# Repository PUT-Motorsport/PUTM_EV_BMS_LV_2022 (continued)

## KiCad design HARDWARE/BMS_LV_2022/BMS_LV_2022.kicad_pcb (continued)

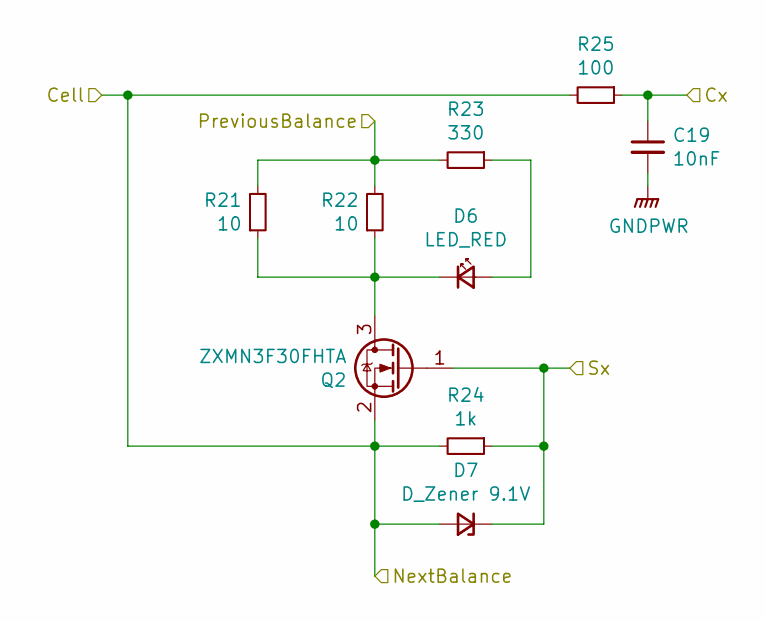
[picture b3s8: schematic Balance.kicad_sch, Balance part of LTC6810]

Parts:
C19: 10nF; C_0603_1608Metric
D6: LED_RED; LED_0603_1608Metric
D7: D_Zener 9.1V; D_SOD-323; Part Number BZX384-C9V1.115
Q2: ZXMN3F30FHTA; SOT-23
R21, R22: 10; R_2512_6332Metric; Part Number CHP2512AFX-10R0ELF
R23: 330; R_0603_1608Metric
R24: 1k; R_0603_1608Metric
R25: 100; R_0603_1608Metric

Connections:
+BATT: R21.2, R22.2, R23.2; also elsewhere on the board
/LTC6810/Balance1/Cx: C19.1, R25.1; also elsewhere on the board
/LTC6810/Balance1/Sx: D7.1 (K), Q2.1 (G), R24.1; also elsewhere on the board
/LTC6810/CellBalance2: D7.2 (A), Q2.2 (S), R24.2, R25.2; also elsewhere on the board
GND: C19.2; also elsewhere on the board
unnamed: D6.2 (A), R23.1
unnamed: D6.1 (K), Q2.3 (D), R21.1, R22.1

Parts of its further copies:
C20, C21, C22, C23, C24: 10nF; C_0603_1608Metric
D8, D10, D12, D14, D16: LED_RED; LED_0603_1608Metric
D9, D11, D13, D15, D17: D_Zener 9.1V; D_SOD-323; Part Number BZX384-C9V1.115
Q3, Q4, Q5, Q6, Q7: ZXMN3F30FHTA; SOT-23
R26, R27, R31, R32, R36, R37, R41, R42, R46, R47: 10; R_2512_6332Metric; Part Number CHP2512AFX-10R0ELF
R28, R33, R38, R43, R48: 330; R_0603_1608Metric
R29, R34, R39, R44, R49: 1k; R_0603_1608Metric
R30, R35, R40, R45, R50: 100; R_0603_1608Metric

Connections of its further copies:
/LTC6810/Balance2/Cx: C20.1, R30.1; also elsewhere on the board
/LTC6810/Balance2/Sx: D9.1 (K), Q3.1 (G), R29.1; also elsewhere on the board
/LTC6810/Balance3/Cx: C21.1, R35.1; also elsewhere on the board
/LTC6810/Balance3/Sx: D11.1 (K), Q4.1 (G), R34.1; also elsewhere on the board
/LTC6810/Balance4/Cx: C22.1, R40.1; also elsewhere on the board
/LTC6810/Balance4/Sx: D13.1 (K), Q5.1 (G), R39.1; also elsewhere on the board
/LTC6810/Balance5/Cx: C23.1, R45.1; also elsewhere on the board
/LTC6810/Balance5/Sx: D15.1 (K), Q6.1 (G), R44.1; also elsewhere on the board
/LTC6810/Balance6/Cx: C24.1, R50.1; also elsewhere on the board
/LTC6810/Balance6/Sx: D17.1 (K), Q7.1 (G), R49.1; also elsewhere on the board
/LTC6810/CellBalance2: R26.2, R27.2, R28.2; also elsewhere on the board
/LTC6810/CellBalance3: D9.2 (A), Q3.2 (S), R29.2, R30.2, R31.2, R32.2, R33.2; also elsewhere on the board
/LTC6810/CellBalance4: D11.2 (A), Q4.2 (S), R34.2, R35.2, R36.2, R37.2, R38.2; also elsewhere on the board
/LTC6810/CellBalance5: D13.2 (A), Q5.2 (S), R39.2, R40.2, R41.2, R42.2, R43.2; also elsewhere on the board
/LTC6810/CellBalance6: D15.2 (A), Q6.2 (S), R44.2, R45.2, R46.2, R47.2, R48.2; also elsewhere on the board
GND: C20.2, C21.2, C22.2, C23.2, C24.2, D17.2 (A), Q7.2 (S), R49.2, R50.2; also elsewhere on the board
unnamed: D8.2 (A), R28.1
unnamed: D8.1 (K), Q3.3 (D), R26.1, R27.1
unnamed: D10.2 (A), R33.1
unnamed: D10.1 (K), Q4.3 (D), R31.1, R32.1
unnamed: D12.2 (A), R38.1
unnamed: D12.1 (K), Q5.3 (D), R36.1, R37.1
unnamed: D14.2 (A), R43.1
unnamed: D14.1 (K), Q6.3 (D), R41.1, R42.1
unnamed: D16.2 (A), R48.1
unnamed: D16.1 (K), Q7.3 (D), R46.1, R47.1

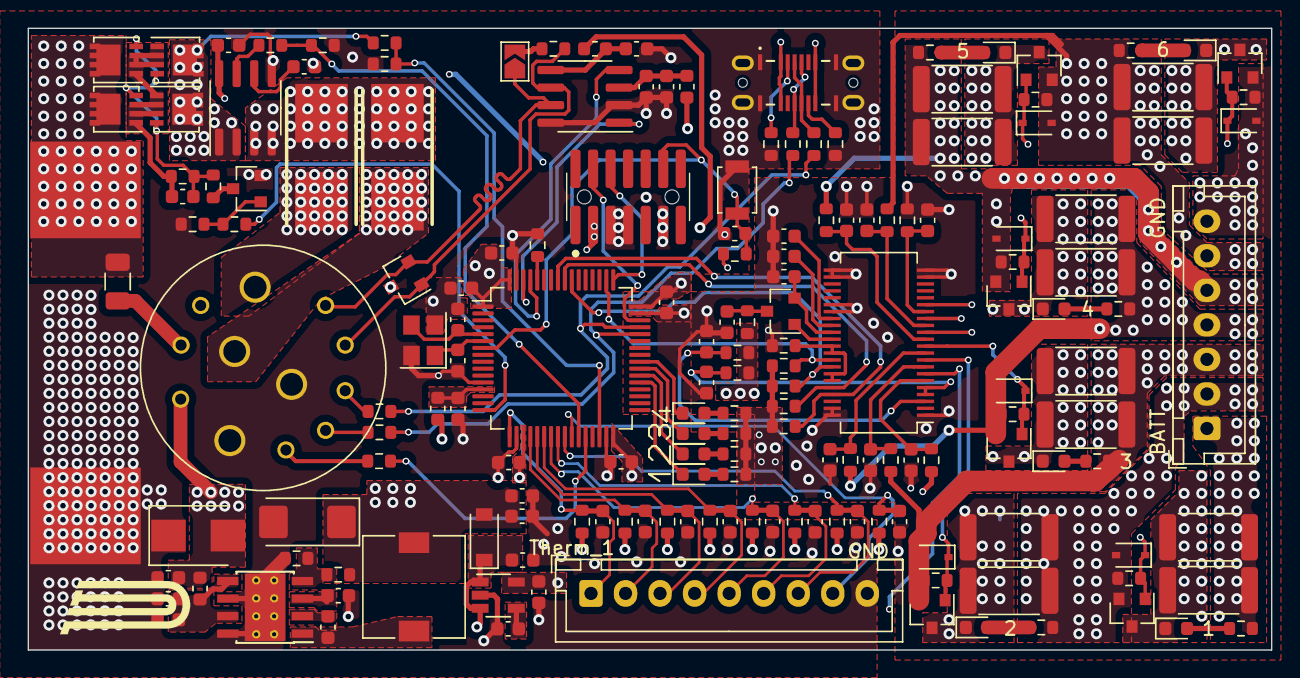
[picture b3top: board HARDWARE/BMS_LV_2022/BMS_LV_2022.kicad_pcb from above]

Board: 4 copper layers, 90.0 x 45.0 mm, 171 parts (1 on the bottom side), 108 nets.

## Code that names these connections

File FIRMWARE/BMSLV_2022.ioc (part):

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Mcu.Name=STM32L4P5R(G-E)Tx
Mcu.Package=LQFP64
Mcu.UserName=STM32L4P5RETx
PA11.Mode=Device_Only
PA11.Signal=USB_OTG_FS_DM
PA12.GPIOParameters=GPIO_PuPd
PA12.GPIO_PuPd=GPIO_PULLUP
PA12.Mode=Device_Only
PA12.Signal=USB_OTG_FS_DP
PA13\ (JTMS/SWDIO).GPIOParameters=GPIO_Label
PA13\ (JTMS/SWDIO).GPIO_Label=SW_DIO
PA13\ (JTMS/SWDIO).Mode=Serial_Wire
PA13\ (JTMS/SWDIO).Signal=SYS_JTMS-SWDIO
PA14\ (JTCK/SWCLK).GPIOParameters=GPIO_Label
PA14\ (JTCK/SWCLK).GPIO_Label=SW_CLK
PA14\ (JTCK/SWCLK).Mode=Serial_Wire
PA14\ (JTCK/SWCLK).Signal=SYS_JTCK-SWCLK
PA15\ (JTDI).GPIOParameters=GPIO_Speed,PinState,GPIO_Label
PA15\ (JTDI).GPIO_Label=SPI1_CS
PA15\ (JTDI).GPIO_Speed=GPIO_SPEED_FREQ_VERY_HIGH
PA15\ (JTDI).PinState=GPIO_PIN_RESET
PA15\ (JTDI).Signal=GPIO_Output
PA2.GPIOParameters=GPIO_Speed,PinState,GPIO_Label
PA2.GPIO_Label=EFUSE
PA2.GPIO_Speed=GPIO_SPEED_FREQ_VERY_HIGH
PA2.PinState=GPIO_PIN_RESET
PA2.Signal=GPIO_Output
PA3.GPIOParameters=GPIO_Label
PA3.GPIO_Label=THERM_1
PA3.Signal=ADCx_IN8
PA4.GPIOParameters=GPIO_Label
PA4.GPIO_Label=THERM_2
PA4.Signal=ADCx_IN9
PA5.GPIOParameters=GPIO_Label
PA5.GPIO_Label=THERM_3
PA5.Signal=ADCx_IN10
PA6.GPIOParameters=GPIO_Label
PA6.GPIO_Label=THERM_4
PA6.Signal=ADCx_IN11
PA7.GPIOParameters=GPIO_Label
PA7.GPIO_Label=THERM_5
PA7.Signal=ADCx_IN12
PB0.GPIOParameters=GPIO_Label
PB0.GPIO_Label=THERM_8
PB0.Signal=ADCx_IN15
PB1.GPIOParameters=GPIO_Label
PB1.GPIO_Label=CURRENT_SENSOR
PB1.Signal=ADCx_IN16
PB11.GPIOParameters=GPIO_Speed,GPIO_Label
PB11.GPIO_Label=FUSE_VOLTAGE
PB11.GPIO_Speed=GPIO_SPEED_FREQ_VERY_HIGH
PB11.Signal=GPIO_Output
PB2.GPIOParameters=GPIO_PuPd,GPIO_Label
PB2.GPIO_Label=INTERLOCK
PB2.GPIO_PuPd=GPIO_PULLUP
PB2.Signal=GPIO_Input
PB3\ (JTDO/TRACESWO).Mode=Full_Duplex_Master
PB3\ (JTDO/TRACESWO).Signal=SPI1_SCK
PB4\ (NJTRST).GPIOParameters=GPIO_PuPd
PB4\ (NJTRST).GPIO_PuPd=GPIO_PULLUP
PB4\ (NJTRST).Mode=Full_Duplex_Master
PB4\ (NJTRST).Signal=SPI1_MISO
PB5.Mode=Full_Duplex_Master
PB5.Signal=SPI1_MOSI
PB8.Mode=CAN_Activate
PB8.Signal=CAN1_RX
PB9.Mode=CAN_Activate
PB9.Signal=CAN1_TX
PC4.GPIOParameters=GPIO_Label
PC4.GPIO_Label=THERM_6
PC4.Signal=ADCx_IN13
PC5.GPIOParameters=GPIO_Label
PC5.GPIO_Label=THERM_7
PC5.Signal=ADCx_IN14
PC6.GPIOParameters=GPIO_Speed,PinState,GPIO_PuPd,GPIO_Label
PC6.GPIO_Label=LED_1
PC6.GPIO_PuPd=GPIO_NOPULL
PC6.GPIO_Speed=GPIO_SPEED_FREQ_VERY_HIGH
PC6.PinState=GPIO_PIN_SET
PC6.Signal=GPIO_Output
PC7.GPIOParameters=GPIO_Speed,PinState,GPIO_PuPd,GPIO_Label
PC7.GPIO_Label=LED_2
PC7.GPIO_PuPd=GPIO_NOPULL
PC7.GPIO_Speed=GPIO_SPEED_FREQ_VERY_HIGH
PC7.PinState=GPIO_PIN_SET
PC7.Signal=GPIO_Output
PC8.GPIOParameters=GPIO_Speed,PinState,GPIO_PuPd,GPIO_Label
PC8.GPIO_Label=LED_3
PC8.GPIO_PuPd=GPIO_NOPULL
PC8.GPIO_Speed=GPIO_SPEED_FREQ_VERY_HIGH
PC8.PinState=GPIO_PIN_SET
PC8.Signal=GPIO_Output
PC9.GPIOParameters=GPIO_Speed,PinState,GPIO_PuPd,GPIO_Label
PC9.GPIO_Label=LED_4
PC9.GPIO_PuPd=GPIO_NOPULL
PC9.GPIO_Speed=GPIO_SPEED_FREQ_VERY_HIGH
PC9.PinState=GPIO_PIN_SET
PC9.Signal=GPIO_Output
PH0-OSC_IN\ (PH0).Mode=HSE-External-Oscillator
PH0-OSC_IN\ (PH0).Signal=RCC_OSC_IN
PH1-OSC_OUT\ (PH1).Mode=HSE-External-Oscillator
PH1-OSC_OUT\ (PH1).Signal=RCC_OSC_OUT
RCC.HSE_VALUE=16000000
RCC.SYSCLKFreq_VALUE=64000000
RCC.SYSCLKSource=RCC_SYSCLKSOURCE_PLLCLK
board=custom

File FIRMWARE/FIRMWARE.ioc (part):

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Mcu.Name=STM32G484RETx
Mcu.Package=LQFP64
Mcu.UserName=STM32G484RETx
PA0.GPIOParameters=GPIO_Label
PA0.GPIO_Label=THERM_1
PA0.Mode=IN1-Single-Ended
PA0.Signal=ADC1_IN1
PA1.GPIOParameters=GPIO_Label
PA1.GPIO_Label=THERM_2
PA1.Mode=IN2-Single-Ended
PA1.Signal=ADC1_IN2
PA11.Mode=Device
PA11.Signal=USB_DM
PA12.Mode=Device
PA12.Signal=USB_DP
PA13.Mode=Serial_Wire
PA13.Signal=SYS_JTMS-SWDIO
PA14.Mode=Serial_Wire
PA14.Signal=SYS_JTCK-SWCLK
PA2.GPIOParameters=GPIO_Label
PA2.GPIO_Label=THERM_3
PA2.Mode=IN3-Single-Ended
PA2.Signal=ADC1_IN3
PA3.GPIOParameters=GPIO_Label
PA3.GPIO_Label=THERM_7
PA3.Mode=IN4-Single-Ended
PA3.Signal=ADC1_IN4
PA5.GPIOParameters=GPIO_Speed
PA5.GPIO_Speed=GPIO_SPEED_FREQ_VERY_HIGH
PA5.Mode=Full_Duplex_Master
PA5.Signal=SPI1_SCK
PA6.GPIOParameters=GPIO_Speed,GPIO_PuPd
PA6.GPIO_PuPd=GPIO_PULLUP
PA6.GPIO_Speed=GPIO_SPEED_FREQ_VERY_HIGH
PA6.Mode=Full_Duplex_Master
PA6.Signal=SPI1_MISO
PA7.GPIOParameters=GPIO_Speed
PA7.GPIO_Speed=GPIO_SPEED_FREQ_VERY_HIGH
PA7.Mode=Full_Duplex_Master
PA7.Signal=SPI1_MOSI
PA8.GPIOParameters=GPIO_Speed,GPIO_Label
PA8.GPIO_Label=SPI1_CS
PA8.GPIO_Speed=GPIO_SPEED_FREQ_VERY_HIGH
PA8.Signal=GPIO_Output
PB0.GPIOParameters=GPIO_Label
PB0.GPIO_Label=CAN_STANDBY
PB0.Signal=GPIO_Output
PB11.GPIOParameters=GPIO_Speed,GPIO_Label
PB11.GPIO_Label=EFUSE
PB11.GPIO_Speed=GPIO_SPEED_FREQ_VERY_HIGH
PB11.Signal=GPIO_Output
PB12.GPIOParameters=GPIO_Label
PB12.GPIO_Label=CAN_RX
PB12.Mode=FDCAN_Activate
PB12.Signal=FDCAN2_RX
PB13.GPIOParameters=GPIO_Label
PB13.GPIO_Label=CAN_TX
PB13.Mode=FDCAN_Activate
PB13.Signal=FDCAN2_TX
PB14.GPIOParameters=GPIO_Label
PB14.GPIO_Label=THERM_8
PB14.Mode=IN5-Single-Ended
PB14.Signal=ADC1_IN5
PB15.GPIOParameters=GPIO_Label
PB15.GPIO_Label=FUSE_VOLTAGE
PB15.Mode=IN15-Single-Ended
PB15.Signal=ADC2_IN15
PB2.GPIOParameters=GPIO_Label
PB2.GPIO_Label=CURRENT_SENSOR
PB2.Mode=IN12-Single-Ended
PB2.Signal=ADC2_IN12
PB4.GPIOParameters=GPIO_Speed,GPIO_Label
PB4.GPIO_Label=RED
PB4.GPIO_Speed=GPIO_SPEED_FREQ_VERY_HIGH
PB4.Signal=GPIO_Output
PB5.GPIOParameters=GPIO_Speed,GPIO_Label
PB5.GPIO_Label=GREEN
PB5.GPIO_Speed=GPIO_SPEED_FREQ_VERY_HIGH
PB5.Signal=GPIO_Output
PB6.GPIOParameters=GPIO_Speed,GPIO_Label
PB6.GPIO_Label=YELLOW
PB6.GPIO_Speed=GPIO_SPEED_FREQ_VERY_HIGH
PB6.Signal=GPIO_Output
PC0.GPIOParameters=GPIO_Label
PC0.GPIO_Label=THERM_4
PC0.Mode=IN6-Single-Ended
PC0.Signal=ADC1_IN6
PC1.GPIOParameters=GPIO_Label
PC1.GPIO_Label=THERM_5
PC1.Mode=IN7-Single-Ended
PC1.Signal=ADC1_IN7
PC10.GPIOParameters=GPIO_Label
PC10.GPIO_Label=UART_TX
PC10.Mode=Asynchronous
PC10.Signal=UART4_TX
PC11.GPIOParameters=GPIO_Label
PC11.GPIO_Label=UART_RX
PC11.Mode=Asynchronous
PC11.Signal=UART4_RX
PC2.GPIOParameters=GPIO_Label
PC2.GPIO_Label=THERM_6
PC2.Mode=IN8-Single-Ended
PC2.Signal=ADC1_IN8
PC6.GPIOParameters=GPIO_PuPd,GPIO_Label
PC6.GPIO_Label=INTERLOCK
PC6.GPIO_PuPd=GPIO_PULLUP
PC6.Signal=GPIO_Input
RCC.HSE_Timout=1000
RCC.HSE_VALUE=32000000
RCC.SYSCLKFreq_VALUE=64000000
RCC.SYSCLKSource=RCC_SYSCLKSOURCE_PLLCLK
board=custom

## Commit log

2021-11-12 gitinit for c++/kicad
2021-11-12 project structure
2021-11-12 Create LICENSE
2021-11-22 Hardware Update 1
    +CAN section
    +LTC6810 section
    +Thermistors section
2021-11-23 gitignore update
2021-11-29 Hardware Update 2
    First verison of the scheme finished
    +Power section
    +eFuse section
    +Current Sensor section
    +Connectors section
    +Debug LEDs
2021-12-13 Hardware update; -changes after team review;
2021-12-14 Electrical Rules Checker fixes
2021-12-15 Most of the footprints added
2021-12-17 PCB layout init
2021-12-18 Some footprint changes
2021-12-31 Thermistors change
2022-01-09 PCB update
    Parts changed due to smaller footprints
2022-01-14 PCB Layout Update
    Some work on PCB Layout
    + AS214-97PN (connector) 3D model added
2022-01-14 PCB Layout Update 2
2022-01-19 PCB Layout Update 3
2022-01-19 Power planes added
2022-01-21 PCB Routing Update
2022-01-22 PCB Routing Update 2
2022-01-22 Small bug fixes
2022-01-23 Bug fixes on PCB
2022-01-23 HARDWARE Release V1.0
2022-01-24 Changes in V1.0
    -Fuse holder change
    -Autosport conn angle change
2022-01-24 Last Changes in V1.0
    Fuse voltage measurement added
2022-03-15 Balance section -> specific transistor added
2022-03-15 Block diagram added
2022-03-15 Block diagram -> README
2022-03-28 Firmware init- ioc file
2022-05-05 PCB test on 2021 code, FreeRTOS init
2022-05-07 Firmware Update
    +New FreeRTOS tasks added
    +tc_task completed
    +soc_update_task in progress
    +ltc_library created
2022-05-13 Balance task
    -some changes in soc_update_task.cpp
    -first version of balance_task
    -Interlock pin added on PB2
    -Charging struct added
    -defines needed to balance_task added
2022-05-15 error handling
    HARDWARE:
    -transistor change (only proper name added)
    FIRMWARE:
    -error handling functions added
    -balance_task small changes
    -min_max_cell_voltage function changed to work on global variables
2022-05-17 ETL library
    -ETL library added
    -bug fixes
    -comm_err_task work in progress
    -soc class moved to global struct in main.h
2022-05-17 Code review 1.0
2022-05-19 comm_err_task update
2022-05-21 USB added, CAN Library added
    -USB added
    -CAN library added
    -serial communication function added
    -error checker finished
    -some small all-around changes
2022-05-22 Renewed project
    Due to bugs I couldn't resolve, the new project has been created.
    -structs and defines were moved to new file
    -some small bugs were fixed
2022-05-25 FIXES
    -DMA fixed (ioc changes)
    -FreeRTOS fixed (memory per task increased, osDelay in every task)
    -huge fix in current sensor section (I forgot about hardware voltage divider, so I added one on pcb- it looks bad but it works :); it will be an update with that in kicad)
    -can_function added
    -error task lift
    To sum up, verything looks fine, its like alpha version for some serious tests.
2022-05-28 CAN library updated
2022-05-29 Charging interlock logic fixed
2022-06-12 Small fixes
    balance_task -> balance algorythm fixed
    comm_err_task -> added ticks for every communication (serial, CANs)
    -temperature adc physically changed to other pins (Im using 5 temperature sensors in this case) by moving them in connector - thats why there is change in get_temperatures function; now adc 7-3 are v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
2022-06-21 Code review
2022-06-22 Code review fixes, CAN library update
    -few fixes after code review
    -CAN Library update
2022-06-22 CAN library as submodule added
2022-06-27 min_max_voltage fixed
    +small changes in balance task
2022-06-27 Voltage divider in current sensor section added
2022-08-03 temperature measurement disconnection error implemented
2024-03-28 Add CAN Library and file .gitignore Init commit in branch "dev"
2024-03-28 Add RingBuffer library files: source file (*.c) header file (*.h)
2024-03-28 Add Parser library file
    Library reads data from RingBuffer and compares the received commands
2024-03-28 Build file (nothing important)
2024-03-28 Add write data from USB and save this in RingBuffer
2024-03-28 Adding the main condition: battery balancing starts when the interlock is plugged in and a signal from USB "BB_Start" is received
2024-04-04 Code review
    +error check also on command added
    +bool to balance flag added
2024-04-04 Paraser
    Changing the .c extension to .cpp and related code changes
2024-04-04 Ring Buffer Edit
    Adding a library to Ringbuffer that supports uint8_t types and the like
2024-04-04 Global Variables
    changing the values of variables for testing on a real system
2024-04-04 Comm Err Task
    changing the conditions that trigger the error-finding and response functions
2024-04-04 USB File
    Minor changes related to the library
2024-04-04 IDE file [Nothing important]
    Files changing during compilation
2024-04-04 Balance Task
    Changing the conditions for invoking the battery balancing system
2024-04-06 Parser files
    Change of the function that reads from the Ring Buffer, compares commands and reacts to them
2024-04-09 Receiving messages from USB
    improved code for reading and comparing commands coming from USB
    BB_Start -> data.charging.balance_on = true
    BB_Stop -> data.charging.balance_on = false
2024-04-09 Global variable improvement
    changing a global variable from a test value to an actual value
2024-04-09 IDE compile files
2024-04-12 Deleting CAN library for changing as submodule
2024-04-29 Unnecessary files deleted
2024-04-29 New fuses and programming connector added
2024-04-29 Significant changes
    -main connector changed to the other side of the pcb because of using socket connector in the new version
    -changed usb mini to usb-c
    -changed fuse to 2 fuses protecting current path pins separately
    -some minor changes in layout
2024-04-30 Version 2.0
    Grounding corrected and production files added
2024-04-30 v2.0
    the last commit was saved when the project was still launched :)
2024-06-22 CubeIDE migration to latest version, rest of the changes in description
    - clock changed from external oscillator to internal (HSE->HSI) due to some errors (might be a hardware problem but it's hard to change it now when it's on the battery stack already)
    - temperatures measurement changed from 5 to 8 as the battery now is bigger and all the measurements are needed
2024-06-29 Removed submodule FIRMWARE/Core/Inc/PUTM_EV_CAN_LIBRARY
2024-06-29 New CAN Library added as submodule
2024-06-29 submodule updated
2024-06-29 Removed submodule FIRMWARE/Core/Inc/PUTM_EV_CAN_LIBRARY_2024
2024-06-29 Revert to old CAN library because Adam implemented only CANFD methods :c
2024-10-03 FS Poland 2024
    - neutral current sleep commented - it's not good on competition
    - lack of error check when the charger is connected commented
2024-10-12 Ability to enable and disable errors using a UART command
2024-10-12 Add default error detection enabled
2024-10-27 Add display information on UART about status BB and error detect
2024-11-26 Edit symbols in Autosport Connector footprint
2024-11-27 Add CAN communication status display
2024-11-30 Autosport connector scheme updated
2025-03-15 Próba zforsowania ładowania
2025-03-18 giemla czesc dalsza
2025-03-18 koniec gimeli
2025-03-25 Set up for smaller batteries
2025-04-12 Update gitignore
2025-04-12 Cmake file
2025-04-12 Erased unnecessary files
2025-04-12 Update CMakeList file
2026-02-17 Utworzono nowego brancha, bms lv w wersji sandwich
2026-02-19 Na review nie skończone, nowe bezpieczniki, nowe rezystory, zupelnie nowy layout, nowe tranzystory
2026-02-19 Zmieniono polozenie bezpiecznikow, dodano ledy sygnalizujące czy bezpiecznik jest cały
2026-02-22 sync
2026-02-24 Wersja obu plytek gotowa do sprawdzenia
2026-02-25 Add hardware validation
2026-02-25 Update workflows
2026-03-02 Zmiany w power: nowe bezpieczniki, nowy wymienialny layout dla tych bezpiecznikow, dodano diode zenera dla stabilizacji napięcia, zmiany dla control: wyjebany eeprom, przesunięty can, zmieniony layou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
2026-03-03 Routing 65%
2026-03-05 Pierwsza wersja bez błędów DRC/ERC, skończony routing plytki control
2026-03-05 Przejście na trackowanie .step jako large file, uzywając FLS
2026-03-05 Przesunięcie sciezek z jednej warstwy wew aby zwolnic ja na mase
2026-03-07 Rozpoczęto developement drugiej wersji plytki control
2026-03-08 Druga wersja plytki control skonczona, do review
2026-03-08 Przesunięto złącze do thermistorów oraz programator aby nie bylo kolizji, przesunięto tez bezpieczniki
2026-03-10 Kolejna kurwa wersja gotowa, japierdole
2026-03-10 Usunięto masę z pod cewki przetwornicy
2026-03-17 Ulozono silkscreena
2026-03-22 V1.0 ready for release
2026-03-22 V1.0 sync
2026-03-25 Kicad 10 sync, some silkscreen changes
2026-04-07 cubemx including freertos configuration
2026-04-08 setup clean smt32g4 project and cmake config. removed old l4 fies
2026-04-08 code changes
2026-04-08 can commented and json problems solved
2026-04-08 Dodano programator.....
2026-04-08 change main c to main cpp
2026-04-18 update new lib
2026-04-20 Naprawiono: załączanie lv, brak zlącza programatora (XD) oraz brak podłączenia czujnika prądu :9
2026-04-20 Zmieniono ledy, przesunięto pomiar napięcia z czujnika prądu na adc2
2026-04-29 cubemx configuration changes
2026-04-29 minor changes in nvic configuration
2026-05-01 cmake changes
2026-05-01 taske tamplates
    wyczyscilem taski bo sie gimela niezla zrobile ze wzgledu na to ze dodalem opcje aby wszytkie perpiherial files sie generowaly w osobnych bliakch. Bez tego byl problem z kolejnoscia atrybutow
2026-05-01 old lvbms logic migration excluding comm err task (can)
2026-05-02 new can lib
2026-05-04 literowka w cmake
2026-05-22 dziala, bez external clocka
2026-05-26 Poprawki , tvs , programator
2026-05-26 Zmieniono złącze programatora na kątowe
2026-05-29 Dodane zenery, programator w innym miejscu
2026-05-29 Zmiany na pinoutcie programatora
2026-05-29 Poprawnie zrobiony programator
2026-06-06 Zmieniono tvs, dodano znowu uart, poprawiono silkscreen, gotowy na release
2026-06-10 edit readme
2026-06-18 Gotowe do review
